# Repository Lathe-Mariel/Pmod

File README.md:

# Pmod
 Pmod boards
# KiCADのプロジェクト
各ボードは，KiCADのプロジェクトを含みます．  
ガーバーデータは 'output' ディレクトリに入っています．  
Each Pmod board directory has KiCAD project file and garber data.

写真 | ボード | 説明 | その他
---|---|---|---
 | Pmod_7Seg | 7セグLED6桁 | Pmodダブル
 | Pmod_encoder | ロータリエンコーダ | Digilent互換
 | Pmod_PLED | パワーLED | 片面アルミ基板
 | Sugamod_Matrix2 <a href="https://github.com/Lathe-Mariel/Pmod/tree/main/Pmod_Matrix2/output/output.zip">garber file</a> | 2色8x8マトリクスLED | Pmod規格外，6層基板
 | Pmod_A4988 | ステッピングモータドライバA4988
 | Pmod_7LED_8digit | 7セグLED8桁 | 4桁7セグモジュール×2個使用
 | Pmod_US_Speaker | 超音波浮揚 | 超音波トランスジューサ×6モジュール
 | Pmod_Matrix256 | 16x16マトリクスLED | 秋月横長マトリクスLED
 | Pmod_ADC | 10bit 8ch A-Dコンバータ | MCP3008/MCP3208
 | Pmod_SC1602 | 16桁2行キャラクタディスプレー | データ4ビット
 | Pmod_CAN | CAN | TJA1441AT

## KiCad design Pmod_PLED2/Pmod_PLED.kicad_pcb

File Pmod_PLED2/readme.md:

# Pmod Power_ColorLED
 KiCADのプロジェクトになっています．  

 アルミの片面基板を想定しており，JLCPCBで制作後，動作確認してあります．

# BOM

## SS2040FL ショットキダイオード
RGBのうち，RだけVfが低いのでバランス取りとして入れています．  
RGB間の出力もPWMで調整する場合は，ソルダージャンパ直結でヨシッ！

# はんだ付け
アルミ基板なので，まぁ付かないです．  
筆者はホットプレート（100℃設定）に基板を置いた状態ではんだこてで手付けしています．  
はんだこてだけでは，かなり厳しいでしょう．  

# サンプルプログラム
サンプルプログラムです．  
Gowin EDAのプロジェクトになっています．

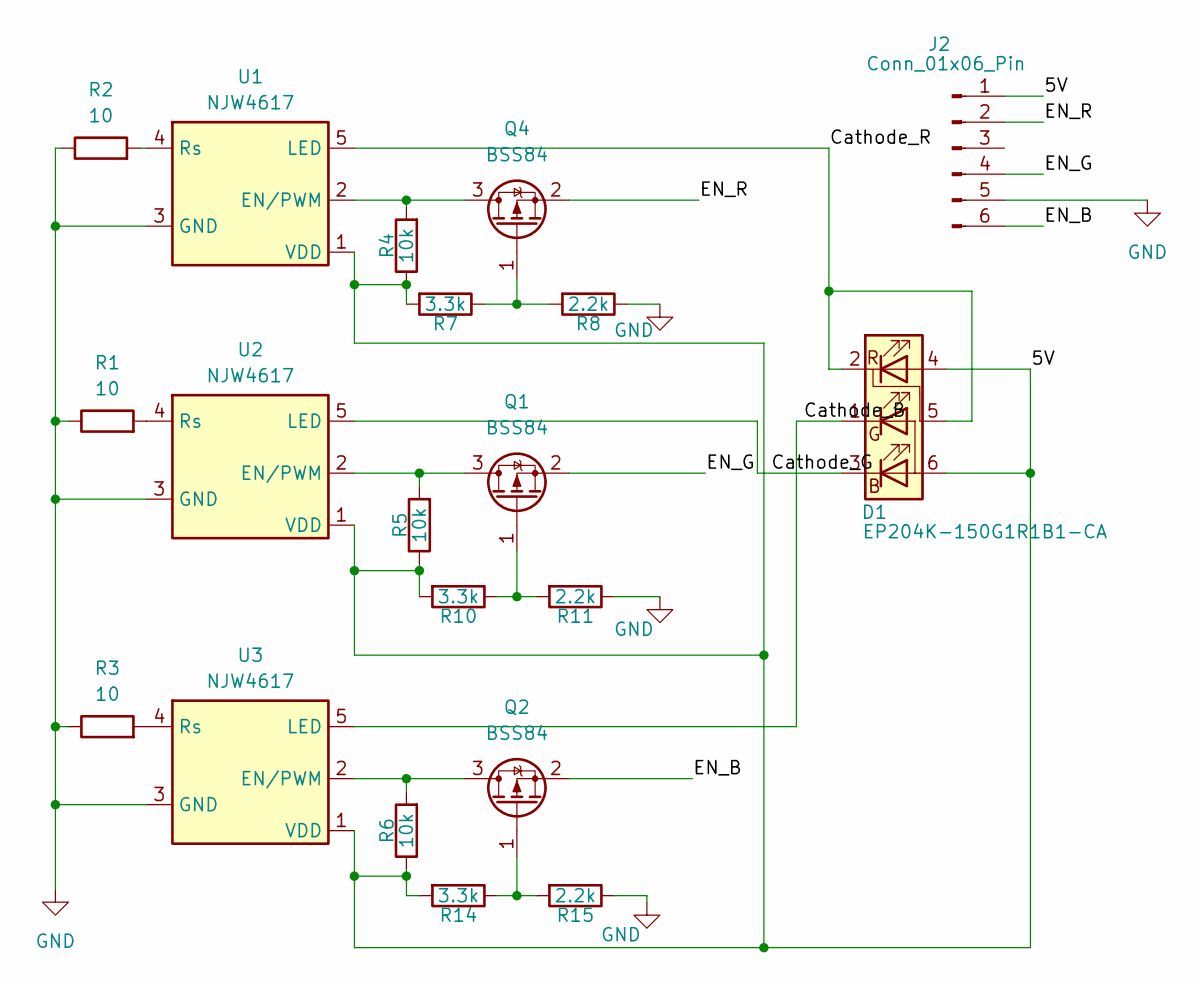
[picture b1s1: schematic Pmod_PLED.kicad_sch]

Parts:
D1: EP204K-150G1R1B1-CA; EP204-150G1R1B1-CA
J2: Conn_01x06_Pin; PinHeader_1x06_P2.54mm_Vertical_SMD_Pin1Left
Q1, Q2, Q4: BSS84; TSOT-23_HandSoldering
R1, R2, R3: 10; R_0603_1608Metric_Pad0.98x0.95mm_HandSolder
R4, R5, R6: 10k; R_0603_1608Metric_Pad0.98x0.95mm_HandSolder
R7, R10, R14: 3.3k; R_0603_1608Metric_Pad0.98x0.95mm_HandSolder
R8, R11, R15: 2.2k; R_0603_1608Metric_Pad0.98x0.95mm_HandSolder
U1, U2, U3: NJW4617; TO-252-5_TabPin3

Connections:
/5V: D1.4 (RA), D1.6 (A), J2.1, R4.1, R5.1, R6.1, R7.2, R10.2, R14.2, U1.1 (VDD), U2.1 (VDD), U3.1 (VDD)
/Cathode_B: D1.1 (GK), U3.5 (LED)
/Cathode_G: D1.3 (BK), U2.5 (LED)
/Cathode_R: D1.2 (RK), D1.5 (RK), U1.5 (LED)
/EN_B: J2.6, Q2.2 (S)
/EN_G: J2.4, Q1.2 (S)
/EN_R: J2.2, Q4.2 (S)
GND: J2.5, R1.1, R2.1, R3.1, R8.1, R11.1, R15.1, U1.3 (GND), U2.3 (GND), U3.3 (GND)
unnamed: Q1.3 (D), R5.2, U2.2 (EN/PWM)
unnamed: Q1.1 (G), R10.1, R11.2
unnamed: Q2.3 (D), R6.2, U3.2 (EN/PWM)
unnamed: Q2.1 (G), R14.1, R15.2
unnamed: Q4.3 (D), R4.2, U1.2 (EN/PWM)
unnamed: Q4.1 (G), R7.1, R8.2
unnamed: R2.2, U1.4 (Rs)
unnamed: R1.2, U2.4 (Rs)
unnamed: R3.2, U3.4 (Rs)

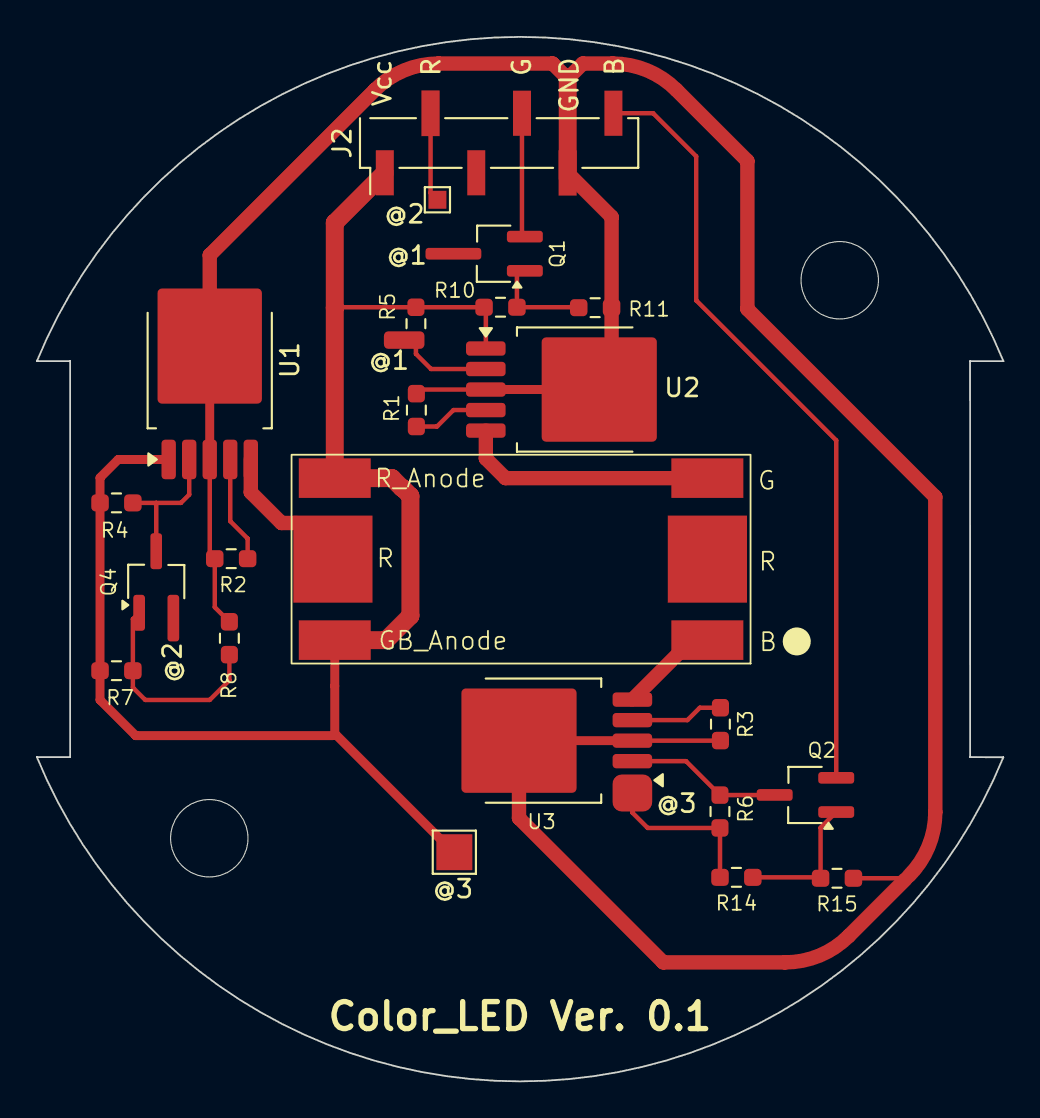
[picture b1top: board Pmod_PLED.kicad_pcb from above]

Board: 2 copper layers, 53.7 x 58.0 mm, 20 parts (0 on the bottom side), 17 nets.

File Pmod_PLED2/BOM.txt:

RoHS2(改正RoHS) (EU)2015/863、10物質、付属品等を除く
表面実装用ピンヘッダ　４０Ｐ　（２×２０）
[2213SM-40G]
1F 12 売場 キャビネット下段



在庫限り・見切り品・処分品
照明用大型フルカラーＬＥＤ　ハイパワー品　ＥＰ２０４Ｋ－１５０Ｇ１Ｒ１Ｂ１－ＣＡ
2021/11/29 500→200円、処分特価!
[EP204K-150G1R1B1-CA]
店員にお問い合わせください



PWM調光機能付き定電流LEDドライバー NJW4617DL3

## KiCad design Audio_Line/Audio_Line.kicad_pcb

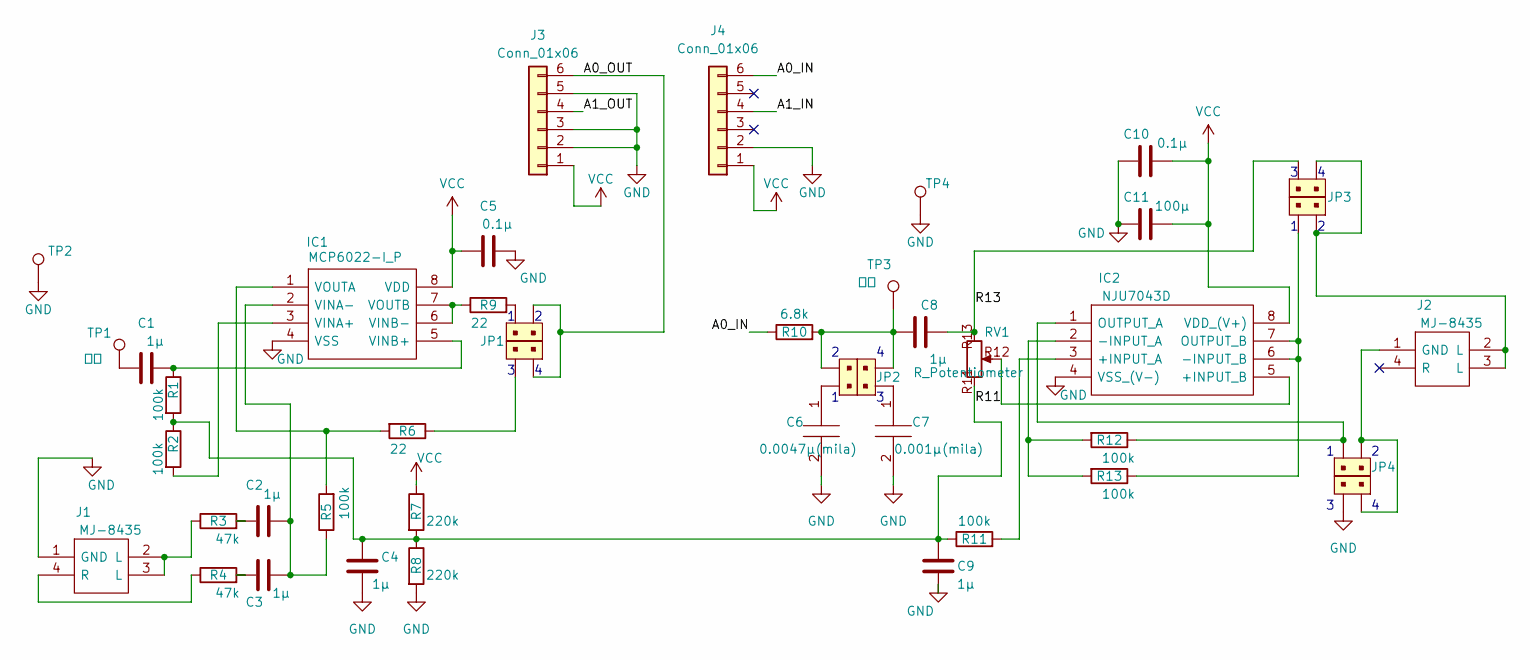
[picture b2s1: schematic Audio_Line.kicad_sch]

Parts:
C1, C2, C3, C4, C8, C9: 1μ; C_0603_1608Metric_Pad1.08x0.95mm_HandSolder
C5, C10: 0.1μ; C_0603_1608Metric_Pad1.08x0.95mm_HandSolder
C6: 0.0047μ(mila); C_Rect_L7.0mm_W2.0mm_P5.00mm; Manufacturer_Part_Number ECQUBAF332MA
C7: 0.001μ(mila); C_Rect_L7.0mm_W3.5mm_P5.00mm; Manufacturer_Part_Number ECQUBAF332MA
C11: 100μ; CP_Radial_D5.0mm_P2.50mm
IC1: MCP6022-I_P; DIP794W56P254L946H432Q8N; Manufacturer_Part_Number MCP6022-I/P
IC2: NJU7043D; DIP762W56P254L880H425Q8N; Manufacturer_Part_Number NJU7043D; Mouser Part Number 513-NJU7043D
J1, J2: MJ-8435; Manufacturer_Part_Number MJ-8435
J3, J4: Conn_01x06; PinHeader_1x06_P2.54mm_Horizontal
JP1, JP2, JP3, JP4, JP11, JP12, JP13, JP14: 22-23-2021; PinHeader_1x02_P2.54mm_Vertical; MPN 22-23-2021; Digi-Key_PN WM4200-ND
R1, R2, R5, R11, R12, R13: 100k; C_0603_1608Metric_Pad1.08x0.95mm_HandSolder
R3, R4: 47k; C_0603_1608Metric_Pad1.08x0.95mm_HandSolder
R6, R9: 22; C_0603_1608Metric_Pad1.08x0.95mm_HandSolder
R7, R8: 220k; C_0603_1608Metric_Pad1.08x0.95mm_HandSolder
R10: 6.8k; C_0603_1608Metric_Pad1.08x0.95mm_HandSolder
RV1: R_Potentiometer; RK09712200HA
TP1: 入力; TestPoint_Loop_D2.50mm_Drill1.0mm
TP2, TP4: TestPoint; TestPoint_Loop_D2.50mm_Drill1.0mm
TP3: 出力; TestPoint_Loop_D2.50mm_Drill1.0mm

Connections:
/A0_IN: J4.6, R10.1
/A0_OUT: J3.6, JP1.2, JP11.1
/A1_IN: J4.4
/A1_OUT: J3.4
/R11: C4.2, C9.2, R1.2, R2.1, R7.2, R8.1, R11.1, RV1.R11 (1)
/R13: C8.2, JP3.1, RV1.R13 (3)
GND: C4.1, C5.1, C6.2, C7.2, C9.1, C10.1, C11.1, IC1.4 (VSS), IC2.4 (VSS_(V-)), J1.1 (GND), J3.2, J3.3, J3.5, J4.2, JP14.2, R8.2, TP2.1, TP4.1
unnamed: C1.2, TP1.1
unnamed: C2.1, R3.2
unnamed: C3.1, R4.2
unnamed: C6.1, JP2.1
unnamed: C7.1, JP12.1
unnamed: C8.1, JP2.2, JP12.2, R10.2, TP3.1
unnamed: IC1.3 (VINA+), R2.2
unnamed: C2.2, C3.2, IC1.2 (VINA-), R5.1
unnamed: C1.1, IC1.5 (VINB+), R1.1
unnamed: IC1.6 (VINB-), IC1.7 (VOUTB), R9.1
unnamed: IC1.1 (VOUTA), R5.2, R6.2
unnamed: IC2.3 (+INPUT_A), R11.2
unnamed: IC2.5 (+INPUT_B), RV1.R12 (2)
unnamed: IC2.2 (-INPUT_A), R12.2, R13.2
unnamed: IC2.6 (-INPUT_B), IC2.7 (OUTPUT_B), JP13.2, R13.1
unnamed: IC2.1 (OUTPUT_A), JP4.1, R12.1
unnamed: J1.2 (L), J1.3 (L), R3.1
unnamed: J1.4 (R), R4.1
unnamed: J2.1 (GND), JP4.2, JP14.1
unnamed: J2.2 (L), J2.3 (L), JP3.2, JP13.1
unnamed: JP1.1, R9.2
unnamed: JP11.2, R6.1
VCC: C5.2, C10.2, C11.2, IC1.8 (VDD), IC2.8 (VDD_(V+)), J3.1, J4.1, R7.1

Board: 2 copper layers, 43 parts (0 on the bottom side), 28 nets, no tracks yet.

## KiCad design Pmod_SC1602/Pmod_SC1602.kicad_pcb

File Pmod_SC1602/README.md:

output/ --------   Gerver data  
sample/ --------   sample project for FPGA  
Pmod_SC1602.kicat_pro ----   KiCAD project

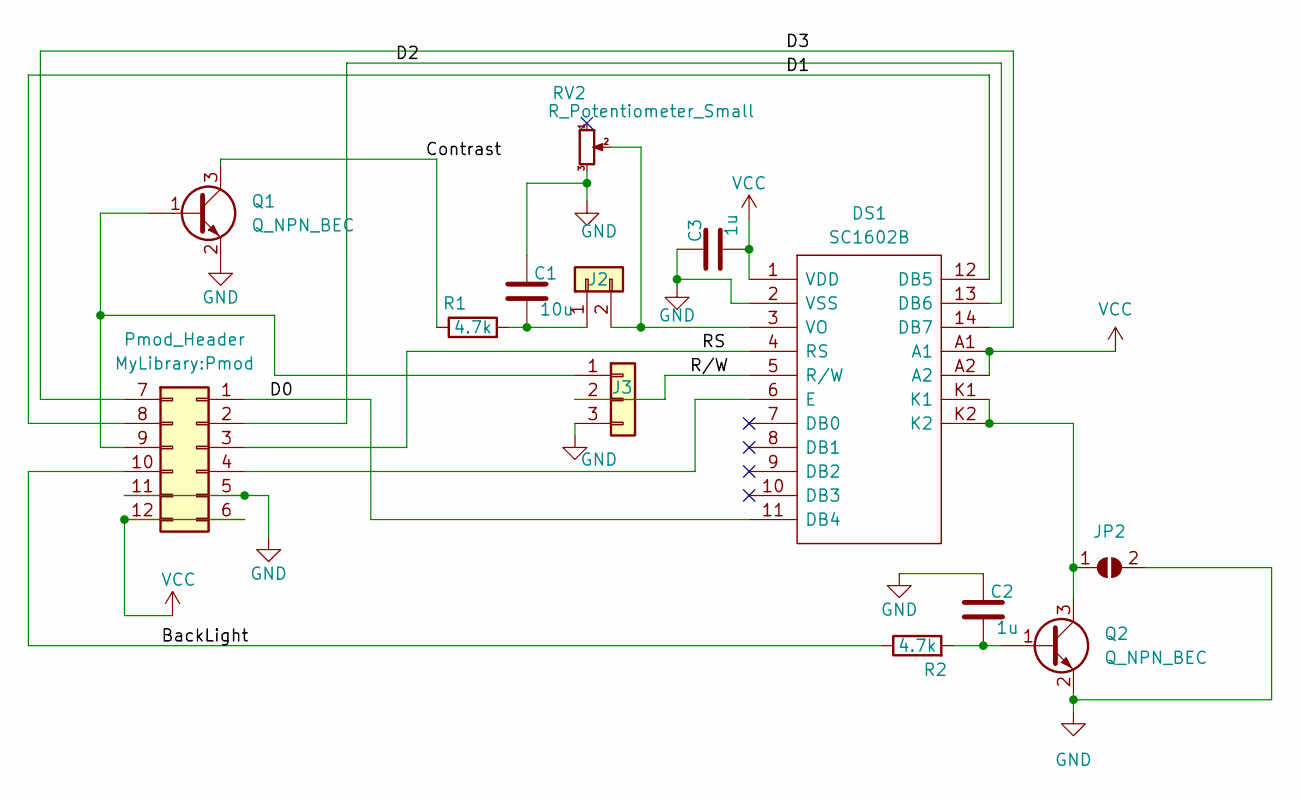
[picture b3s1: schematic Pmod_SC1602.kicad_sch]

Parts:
C1: 10u; C_0805_2012Metric_Pad1.18x1.45mm_HandSolder
C2, C3: 1u; C_0603_1608Metric_Pad1.08x0.95mm_HandSolder
DS1: SC1602B; Manufacturer_Part_Number SC1602B
J1: Pmod_Header; Pmod
J2: Conn_01x02; PinSocket_1x02_P2.54mm_Vertical
J3: Conn_01x03; PinSocket_1x03_P2.54mm_Vertical
JP2: SolderJumper_2_Open; SolderJumper-2_P1.3mm_Open_TrianglePad1.0x1.5mm
Q1, Q2: Q_NPN_BEC; SC-59_Handsoldering
R1, R2: 4.7k; R_0603_1608Metric_Pad0.98x0.95mm_HandSolder
RV2: R_Potentiometer_Small; Potentiometer_Vishay_T73XW_Horizontal

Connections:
/BackLight: J1.10, R2.1
/Contrast: Q1.3 (C), R1.1
/D0: DS1.11 (DB4), J1.1
/D1: DS1.12 (DB5), J1.8
/D2: DS1.13 (DB6), J1.2
/D3: DS1.14 (DB7), J1.7
/RS: DS1.4 (RS), J1.3
/R/W: DS1.5 (R/W), J3.2
GND: C1.2, C2.2, C3.2, DS1.2 (VSS), J1.5, J1.11, J3.3, JP2.2 (B), Q1.2 (E), Q2.2 (E), RV2.3
unnamed: DS1.6 (E), J1.4
unnamed: DS1.3 (VO), J2.2, RV2.2
unnamed: J1.9, J3.1, Q1.1 (B)
unnamed: C1.1, J2.1, R1.2
unnamed: DS1.K1, DS1.K2, JP2.1 (A), Q2.3 (C)
unnamed: C2.1, Q2.1 (B), R2.2
VCC: C3.1, DS1.1 (VDD), DS1.A1, DS1.A2, J1.6, J1.12

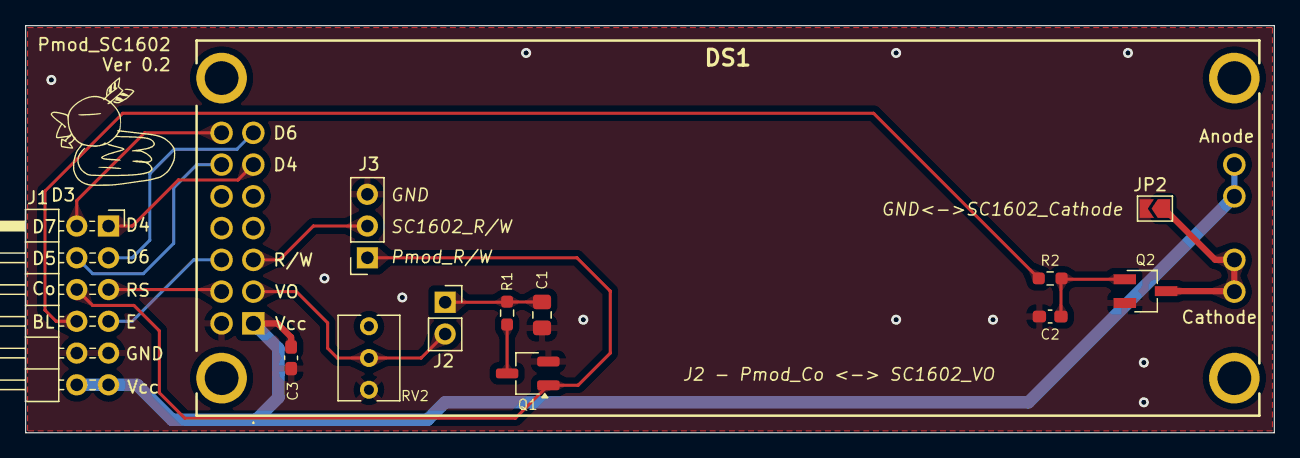
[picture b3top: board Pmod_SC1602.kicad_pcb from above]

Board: 2 copper layers, 99.9 x 32.6 mm, 13 parts (0 on the bottom side), 16 nets.

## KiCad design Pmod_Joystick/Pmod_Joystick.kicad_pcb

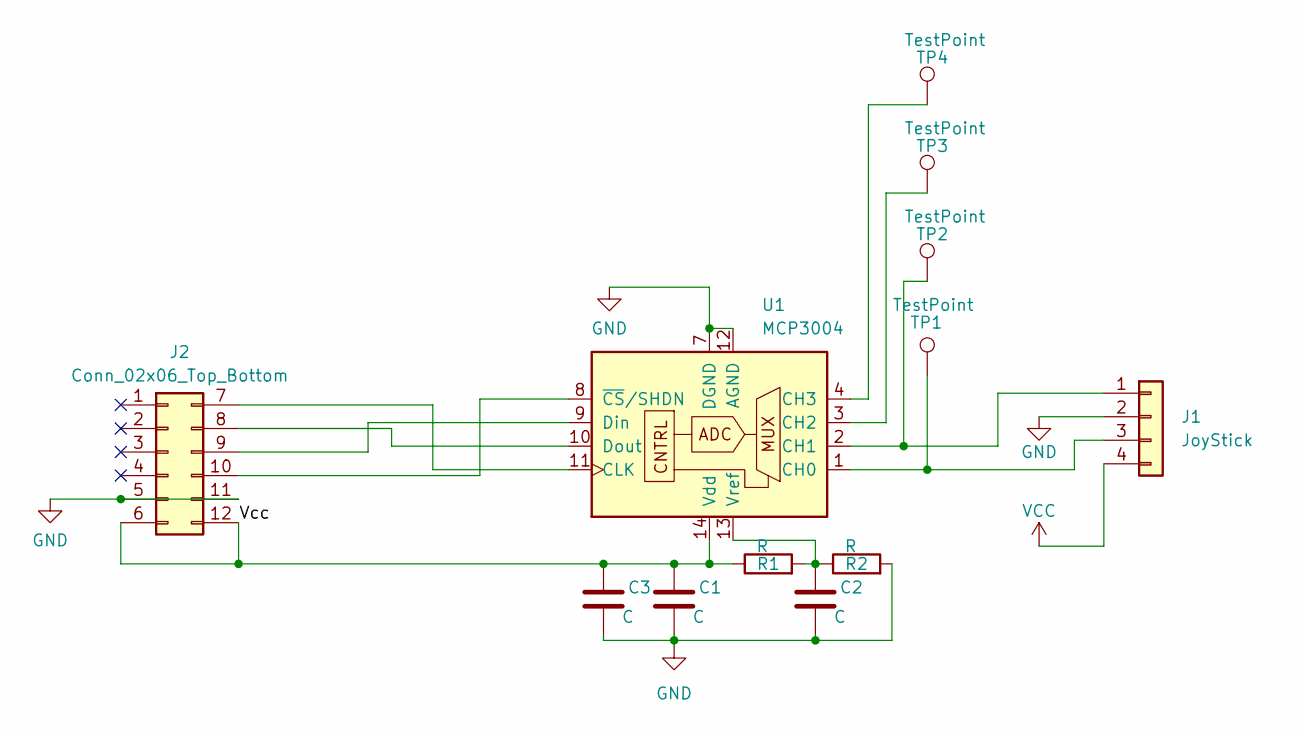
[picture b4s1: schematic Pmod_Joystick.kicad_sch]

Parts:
C1, C2, C3: C; C_0603_1608Metric_Pad1.08x0.95mm_HandSolder
J1: JoyStick; PSP1000_Joystick
J2: Conn_02x06_Top_Bottom; PinSocket_2x06_P2.54mm_Horizontal
R1, R2: R; R_0603_1608Metric_Pad0.98x0.95mm_HandSolder
TP1, TP2, TP3, TP4: TestPoint; TestPoint_THTPad_D1.5mm_Drill0.7mm
U1: MCP3004; TSSOP-14_4.4x5mm_P0.65mm

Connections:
GND: C1.2, C2.2, C3.2, J1.2 (Y), J2.5, J2.11, R2.2, U1.7 (DGND), U1.12 (AGND)
unnamed: J1.3 (GND), TP1.1, U1.1 (CH0)
unnamed: J1.1 (Vcc), TP2.1, U1.2 (CH1)
unnamed: J2.7, U1.11 (CLK)
unnamed: J2.8, U1.10 (Dout)
unnamed: J2.9, U1.9 (Din)
unnamed: J2.10, U1.8 (~CS/SHDN)
unnamed: C1.1, C3.1, J2.6, J2.12, R1.1, U1.14 (Vdd)
unnamed: TP3.1, U1.3 (CH2)
unnamed: TP4.1, U1.4 (CH3)
unnamed: C2.1, R1.2, R2.1, U1.13 (Vref)
VCC: J1.4 (Y)

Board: 2 copper layers, 12 parts (0 on the bottom side), 11 nets, no tracks yet.

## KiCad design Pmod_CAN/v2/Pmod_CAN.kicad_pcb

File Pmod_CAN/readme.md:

# Pmod CAN V2

# Schematics

# BoM

部品(Item) | 内容 | 数量(Qauntity)
--|--|--
チップ抵抗 | 1608 4.7K | 4 | LED(1)，CAN(3)
チップ抵抗 | 1608 10K | 1 | LED
チップ抵抗 | 1608 1/3W 60.4 | 2 | CAN
チップコンデンサ| 1608 0.1μ | 1 | CAN
チップコンデンサ| 1608 10μ | 1 | CAN
チップコンデンサ| 1608 4.7n | 1 | CAN
LED | WS2812B (I-07915) | 3| LED
チップトランジスタ | 2SC3325-Y(I-00628) | 1| LED
AE-XC9306-5V0(秋月) | 昇降圧DC-DCコンバータ | 1 | LED/CAN
ピンヘッダ | アングル・ピンヘッダ(2x6) | 1 | LED/CAN
CANトランシーバ | TJA1441AT(NXP) | 1 | CAN
TVS | | CAN
コモンモードチョークコイル | SDCW3216-2-222TF | CAN
# Sample
　sampleディレクトリにサンプルのFPGA用プロジェクトが入っています．

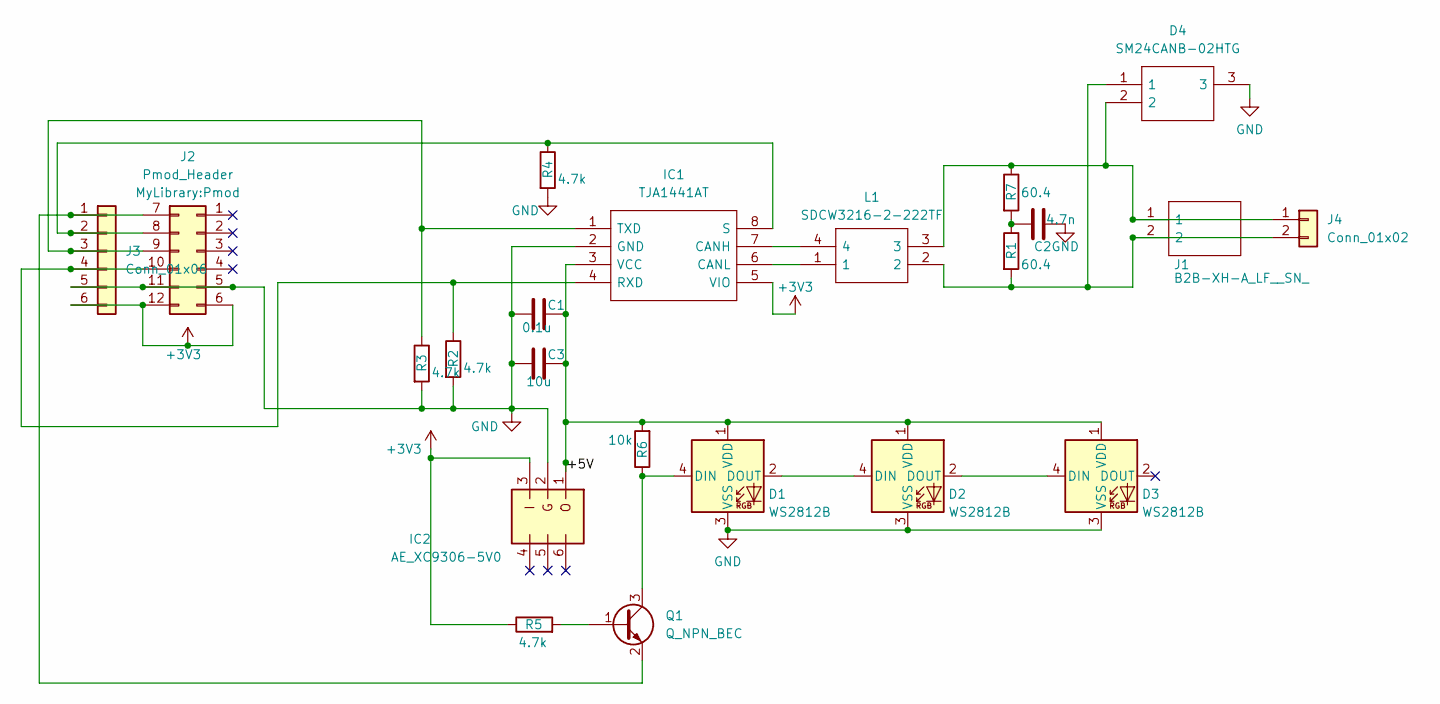
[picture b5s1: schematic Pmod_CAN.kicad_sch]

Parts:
C1: 0.1u; C_0603_1608Metric_Pad1.08x0.95mm_HandSolder
C2: 4.7n; C_0603_1608Metric_Pad1.08x0.95mm_HandSolder
C3: 10u; C_0603_1608Metric_Pad1.08x0.95mm_HandSolder
D1, D2, D3: WS2812B; LED_WS2812B_PLCC4_5.0x5.0mm_P3.2mm
D4: SM24CANB-02HTG; SM24CANB02HTG; Manufacturer_Part_Number SM24CANB-02HTG
IC1: TJA1441AT; SOIC127P600X175-8N; Manufacturer_Part_Number TJA1441AT
IC2: AE_XC9306-5V0; AE-XC9306-5V0
J1: B2B-XH-A_LF__SN_; SHDR2W64P0X250_1X2_740X575X700P; Manufacturer_Part_Number B2B-XH-A(LF)(SN)
J2: Pmod_Header; Pmod
J3: Conn_01x06; PinHeader_1x06_P2.54mm_Vertical
J4: Conn_01x02; PinHeader_1x02_P2.54mm_Vertical
L1: SDCW3216-2-222TF; SDCW32162222TF; Manufacturer_Part_Number SDCW3216-2-222TF
Q1: Q_NPN_BEC; SC-59_Handsoldering
R1, R7: 60.4; R_0603_1608Metric_Pad0.98x0.95mm_HandSolder
R2, R3, R4, R5: 4.7k; R_0603_1608Metric_Pad0.98x0.95mm_HandSolder
R6: 10k; R_0603_1608Metric_Pad0.98x0.95mm_HandSolder

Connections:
+3V3: IC1.5 (VIO), IC2.3, J2.6, J2.12, J3.6, R5.1
/+5V: C1.2, C3.2, D1.1 (VDD), D2.1 (VDD), D3.1 (VDD), IC1.3 (VCC), IC2.1, R6.2
GND: C1.1, C2.2, C3.1, D1.3 (VSS), D2.3 (VSS), D3.3 (VSS), D4.3, IC1.2 (GND), IC2.2 (G), IC2.5 (G), J2.5, J2.11, J3.5, R2.2, R3.2, R4.2
unnamed: C2.1, R1.1, R7.2
unnamed: D1.4 (DIN), Q1.3 (C), R6.1
unnamed: D1.2 (DOUT), D2.4 (DIN)
unnamed: D2.2 (DOUT), D3.4 (DIN)
unnamed: IC1.7 (CANH), L1.4
unnamed: IC1.6 (CANL), L1.1
unnamed: IC1.4 (RXD), J2.10, J3.4, R2.1
unnamed: IC1.8 (S), J2.8, J3.2, R4.1
unnamed: IC1.1 (TXD), J2.9, J3.3, R3.1
unnamed: J2.7, J3.1, Q1.2 (E)
unnamed: D4.2, J1.1, J4.1, L1.3, R7.1
unnamed: D4.1, J1.2, J4.2, L1.2, R1.2
unnamed: Q1.1 (B), R5.2

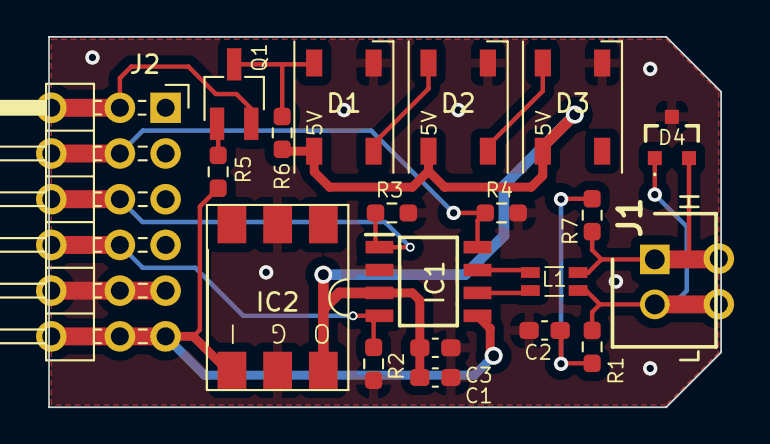
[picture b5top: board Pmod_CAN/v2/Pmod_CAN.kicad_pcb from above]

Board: 2 copper layers, 37.3 x 20.6 mm, 22 parts (0 on the bottom side), 16 nets.

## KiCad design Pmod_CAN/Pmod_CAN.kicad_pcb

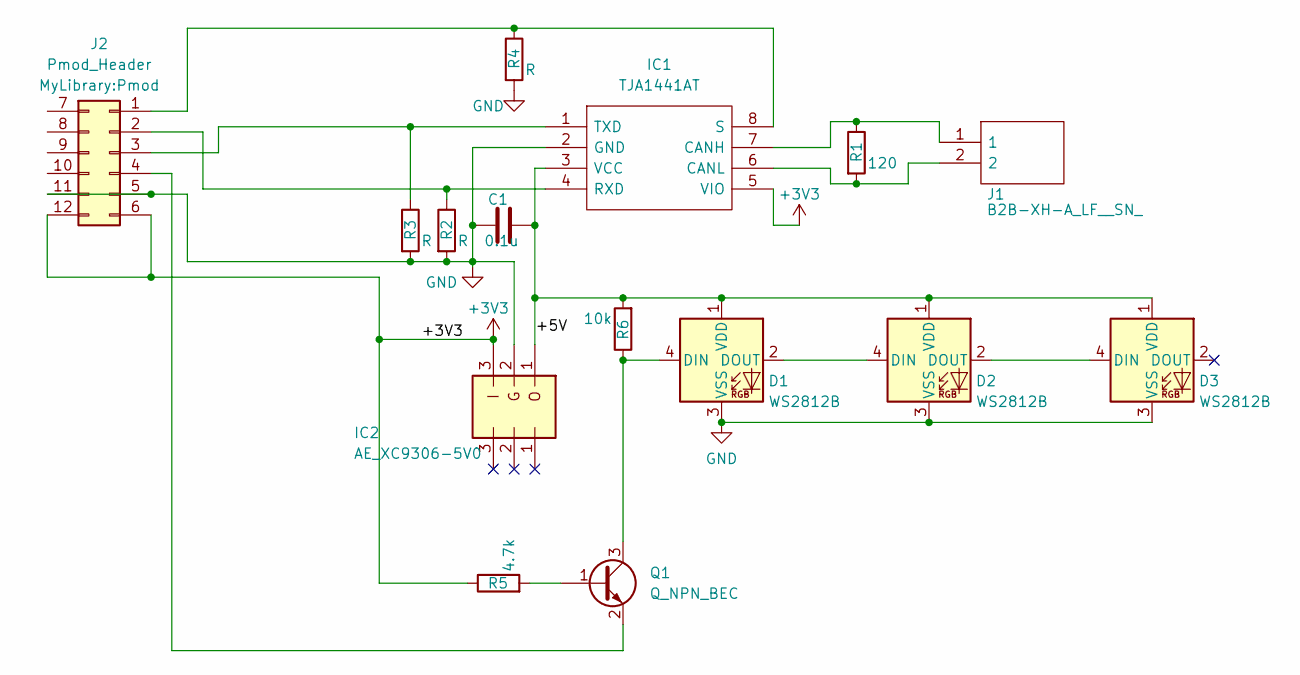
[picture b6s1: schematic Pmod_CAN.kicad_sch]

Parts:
C1: 0.1u; C_0603_1608Metric_Pad1.08x0.95mm_HandSolder
D1: WS2812B; R_Axial_DIN0309_L9.0mm_D3.2mm_P2.54mm_Vertical
D2, D3: WS2812B; LED_WS2812B_PLCC4_5.0x5.0mm_P3.2mm
IC1: TJA1441AT; SOIC127P600X175-8N; Manufacturer_Part_Number TJA1441AT
IC2: AE_XC9306-5V0; AE-XC9306-5V0
J1: B2B-XH-A_LF__SN_; SHDR2W64P0X250_1X2_740X575X700P; Manufacturer_Part_Number B2B-XH-A(LF)(SN)
J2: Pmod_Header; Pmod
Q1: Q_NPN_BEC; SC-59_Handsoldering
R1: 120; R_Axial_DIN0309_L9.0mm_D3.2mm_P2.54mm_Vertical
R2, R3, R4: R; R_0603_1608Metric_Pad0.98x0.95mm_HandSolder
R5: 4.7k; R_0603_1608Metric_Pad0.98x0.95mm_HandSolder
R6: 10k; R_0603_1608Metric_Pad0.98x0.95mm_HandSolder

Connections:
+3V3: IC1.5 (VIO), IC2.3 (I), J2.6, J2.12, R5.1
/+5V: C1.2, D1.1 (VDD), D2.1 (VDD), D3.1 (VDD), IC1.3 (VCC), IC2.1 (O), R6.2
GND: C1.1, D1.3 (VSS), D2.3 (VSS), D3.3 (VSS), IC1.2 (GND), IC2.2 (G), J2.5, J2.11, R2.2, R3.2, R4.2
unnamed: D1.4 (DIN), Q1.3 (C), R6.1
unnamed: D1.2 (DOUT), D2.4 (DIN)
unnamed: D2.2 (DOUT), D3.4 (DIN)
unnamed: IC1.7 (CANH), J1.1, R1.1
unnamed: IC1.6 (CANL), J1.2, R1.2
unnamed: IC1.4 (RXD), J2.2, R2.1
unnamed: IC1.8 (S), J2.1, R4.1
unnamed: IC1.1 (TXD), J2.3, R3.1
unnamed: J2.4, Q1.2 (E)
unnamed: Q1.1 (B), R5.2

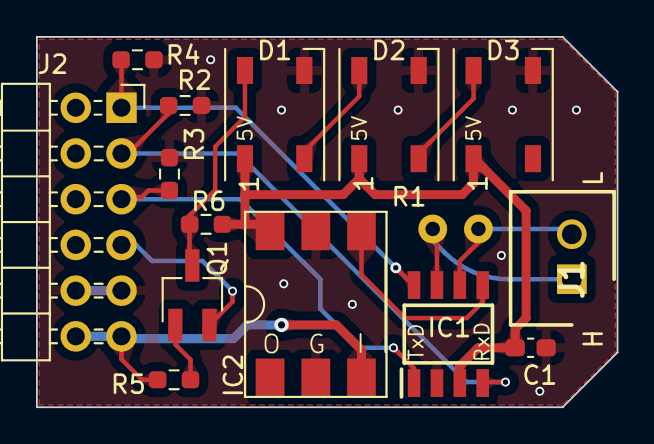
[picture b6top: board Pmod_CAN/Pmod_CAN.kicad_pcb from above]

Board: 2 copper layers, 32.3 x 20.6 mm, 15 parts (0 on the bottom side), 13 nets.

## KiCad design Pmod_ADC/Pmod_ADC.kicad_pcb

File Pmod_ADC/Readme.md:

KiCADで作ったPCBデータです．
Pmodに対応したA-Dコンバータ基板です．  

# Pmod_ADC
8チャネルのADコンバータ・チップ MCP3008/3208をPmodで使うボード．  
8チャネルのアナログ信号を入力できます．  
チャネル1（ch1）については，テストピンもしくはPhone Jackからも入力できます．  

# BoM
網羅はできていませんが，だいたいこんなものがあればよいのではないでしょうか．  

1806抵抗：22Ω，22kΩ，47kΩ  

回路 | 部品(Item) | 説明 | 数量(Qauntity) | No
---|---|---|---|---
U3  | MCP6492T-E/SN | オペアンプ | 1 | I-16239
TP1, TP2(GND) | TEST-1 | テスト端子 | 2 | 
R11, R12 | 金属皮膜チップ抵抗器 220kΩ | 金属皮膜チップ抵抗器1608 1/10W ±0.1% | 2 | 
R6, R7, R10 | チップ抵抗 100kΩ | チップ抵抗 1/10W 100k | 3 | 
R4, R5 | チップ抵抗 47kΩ | チップ抵抗 1/10W 47k | 2 | 
R8, R9 | チップ抵抗 22Ω | チップ抵抗 1/10W 22 | 2 | 
R1, R2 | チップ抵抗 10kΩ | チップ抵抗 1/10W 10k | 2（オプション） | 
J1 | ピンヘッダ | アングル・ピンヘッダ　ダブル(2x6) | 1 | 
C3, C4, C5, C7 | チップコンデンサ 1uF | 積層セラミックコンデンサ 1uF50V 1608 | 4 | 
C2, C6 | チップコンデンサ 0.1uF | 積層セラミックコンデンサ 0.1uF25V 1608 | 2 | 
RV1 | 半固定ボリューム | たて型 3296W 10k | 1（オプション）| P-08939
C1 | 電解コンデンサ | 電解コンデンサMH5 100uF16V | 1 | 
U3 | 10bit 8ch A-Dコンバータ | MCP3008-I/P  | 1 | 

# Schematics

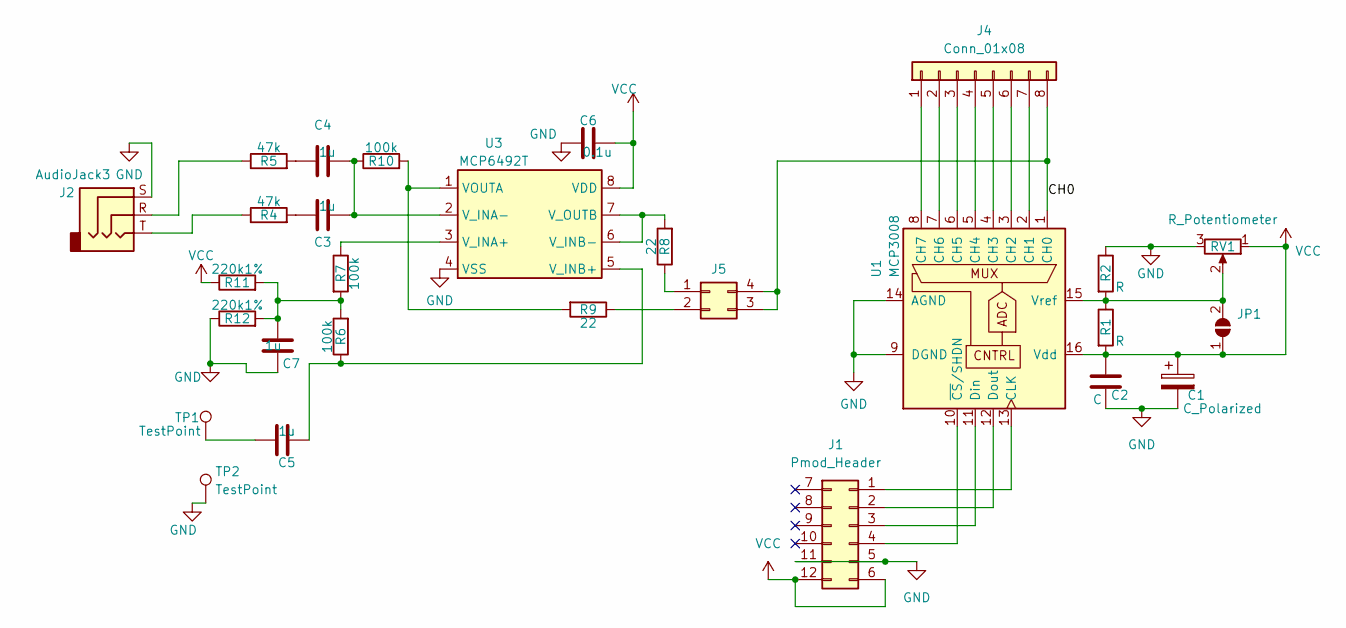
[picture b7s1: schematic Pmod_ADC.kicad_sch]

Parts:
C1: C_Polarized; CP_Radial_D8.0mm_P3.50mm
C2: C; C_0603_1608Metric_Pad1.08x0.95mm_HandSolder
C3, C4, C5, C7: 1u; C_0603_1608Metric_Pad1.08x0.95mm_HandSolder
C6: 0.1u; C_0603_1608Metric_Pad1.08x0.95mm_HandSolder
J1: Pmod_Header; PinHeader_2x06_P2.54mm_Horizontal
J2: AudioJack3; Jack_3.5mm_Switronic_ST-005-G_horizontal
J4: Conn_01x08; TerminalBlock_RND_205-00238_1x08_P5.08mm_Horizontal
J5: Conn_02x02_Counter_Clockwise; PinHeader_2x02_P2.54mm_Vertical
JP1: SolderJumper_2_Open; SolderJumper-2_P1.3mm_Open_TrianglePad1.0x1.5mm
R1, R2: R; R_0603_1608Metric_Pad0.98x0.95mm_HandSolder
R4, R5: 47k; R_0603_1608Metric_Pad0.98x0.95mm_HandSolder
R6, R7, R10: 100k; R_0603_1608Metric_Pad0.98x0.95mm_HandSolder
R8, R9: 22; R_0603_1608Metric_Pad0.98x0.95mm_HandSolder
R11, R12: 220k1%; R_0603_1608Metric_Pad0.98x0.95mm_HandSolder
RV1: R_Potentiometer; TSR3296W203R
TP1, TP2: TestPoint; TestPoint_THTPad_1.5x1.5mm_Drill0.7mm
U1: MCP3008; DIP-16_W7.62mm
U3: MCP6492T; SOIC-8_3.9x4.9mm_P1.27mm

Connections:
/CH0: J4.8, J5.3, J5.4, U1.1 (CH0)
GND: C1.2, C2.2, C6.2, C7.1, J1.5, J1.11, J2.S, R2.1, R12.1, RV1.3, TP2.1, U1.9 (DGND), U1.14 (AGND), U3.4 (VSS)
unnamed: C3.1, R4.2
unnamed: C4.1, R5.2
unnamed: C5.1, TP1.1
unnamed: C7.2, R6.2, R7.2, R11.2, R12.2
unnamed: J1.1, U1.13 (CLK)
unnamed: J1.2, U1.12 (Dout)
unnamed: J1.3, U1.11 (Din)
unnamed: J1.4, U1.10 (~CS/SHDN)
unnamed: J2.R, R5.1
unnamed: J2.T, R4.1
unnamed: J4.1, U1.8 (CH7)
unnamed: J4.2, U1.7 (CH6)
unnamed: J4.3, U1.6 (CH5)
unnamed: J4.4, U1.5 (CH4)
unnamed: J4.5, U1.4 (CH3)
unnamed: J4.6, U1.3 (CH2)
unnamed: J4.7, U1.2 (CH1)
unnamed: J5.1, R8.1
unnamed: J5.2, R9.1
unnamed: JP1.2 (B), R1.1, R2.2, RV1.2, U1.15 (Vref)
unnamed: R9.2, R10.2, U3.1 (VOUTA)
unnamed: R7.1, U3.3 (V_INA+)
unnamed: C3.2, C4.2, R10.1, U3.2 (V_INA-)
unnamed: C5.2, R6.1, U3.5 (V_INB+)
unnamed: R8.2, U3.6 (V_INB-), U3.7 (V_OUTB)
VCC: C1.1, C2.1, C6.1, J1.6, J1.12, JP1.1 (A), R1.2, R11.1, RV1.1, U1.16 (Vdd), U3.8 (VDD)

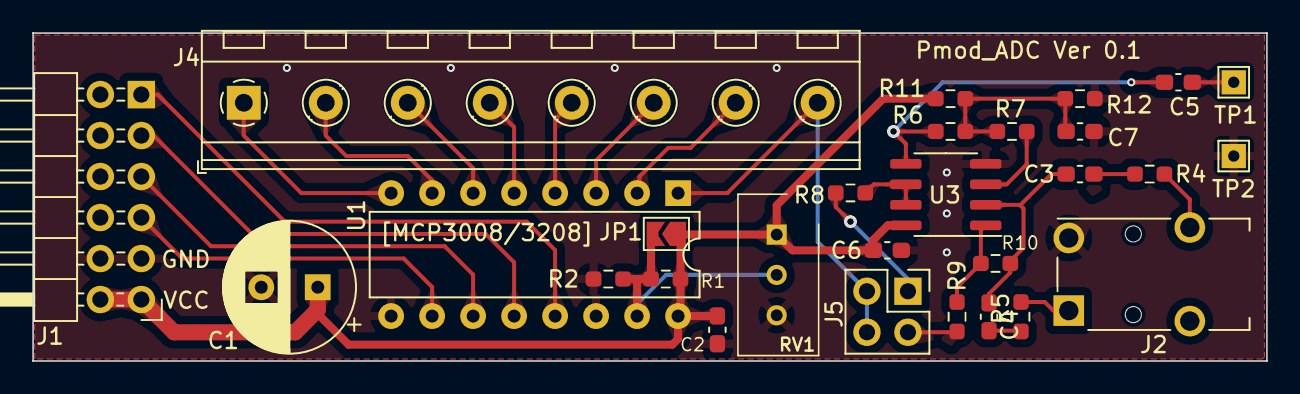
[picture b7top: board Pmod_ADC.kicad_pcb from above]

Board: 2 copper layers, 76.5 x 20.3 mm, 28 parts (0 on the bottom side), 28 nets.

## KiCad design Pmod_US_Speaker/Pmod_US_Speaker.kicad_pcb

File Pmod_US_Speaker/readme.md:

# Playing with Ultra Sonic
超音波浮揚で遊ぶPmodボードです．
2セット使うのがよいです．Upper BoardとLower Boardは同じ生基板を使います（超音波Speakerの取り付け方向が異なる）．

# BoM

部品 | 説明 | 数量
---|---|---
double pin header | Pmod header | 1
IR4428 | Gate Driver IC | 3
DC Jack(SMD) | DC Jack for driving speaker | 1
1608mm SMD Capaciter | chip capaciter 0.1μF V25 | 3
2012mm SMD Capaciter | chip capaciter 10μF V25 | 1

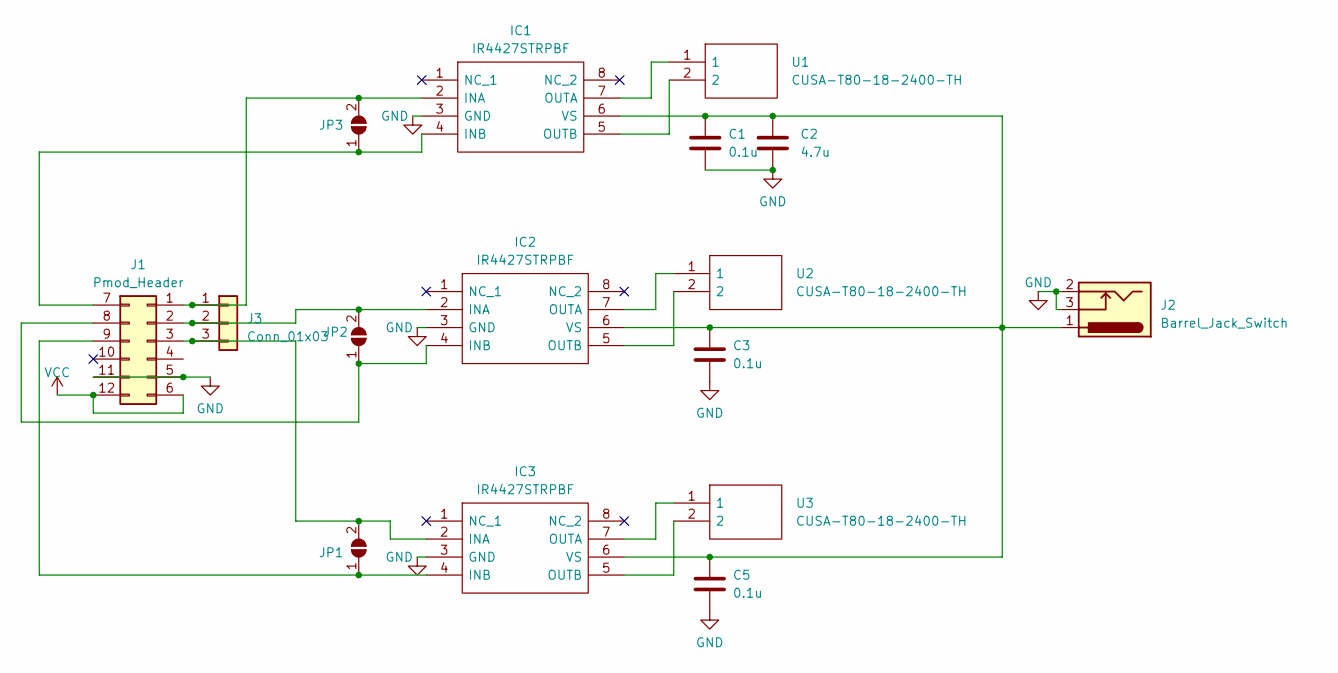
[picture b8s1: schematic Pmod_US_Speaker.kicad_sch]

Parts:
C1, C3, C5: 0.1u; C_0603_1608Metric_Pad1.08x0.95mm_HandSolder
C2: 4.7u; C_0805_2012Metric_Pad1.18x1.45mm_HandSolder
IC1, IC2, IC3: IR4427STRPBF; SOIC127P600X175-8N; Manufacturer_Part_Number IR4427STRPBF
J1: Pmod_Header; PinHeader_2x06_P2.54mm_Vertical
J2: Barrel_Jack_Switch; BarrelJack_CUI_PJ-036AH-SMT_Horizontal
J3: Conn_01x03; PinHeader_1x03_P2.54mm_Vertical
JP1, JP2, JP3: SolderJumper_2_Open; SolderJumper-2_P1.3mm_Open_TrianglePad1.0x1.5mm
U1, U2, U3: CUSA-T80-18-2400-TH; CUSAT80182400TH; Manufacturer_Part_Number CUSA-T80-18-2400-TH

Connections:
GND: C1.2, C2.2, C3.2, C5.2, IC1.3 (GND), IC2.3 (GND), IC3.3 (GND), J1.5, J1.11, J2.2, J2.3
unnamed: IC1.2 (INA), J1.1, J3.1, JP3.2 (B)
unnamed: IC1.4 (INB), J1.7, JP3.1 (A)
unnamed: IC1.7 (OUTA), U1.1
unnamed: IC1.5 (OUTB), U1.2
unnamed: C1.1, C2.1, C3.1, C5.1, IC1.6 (VS), IC2.6 (VS), IC3.6 (VS), J2.1
unnamed: IC2.2 (INA), J1.2, J3.2, JP2.2 (B)
unnamed: IC2.4 (INB), J1.8, JP2.1 (A)
unnamed: IC2.7 (OUTA), U2.1
unnamed: IC2.5 (OUTB), U2.2
unnamed: IC3.2 (INA), J1.3, J3.3, JP1.2 (B)
unnamed: IC3.4 (INB), J1.9, JP1.1 (A)
unnamed: IC3.7 (OUTA), U3.1
unnamed: IC3.5 (OUTB), U3.2
VCC: J1.6, J1.12

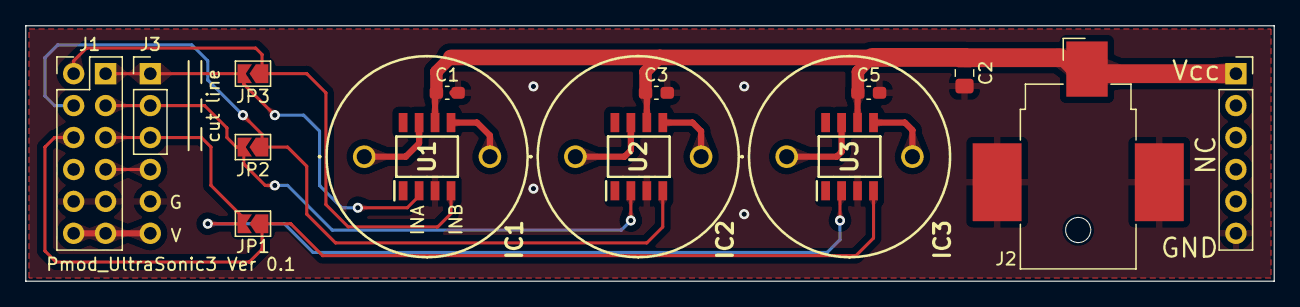
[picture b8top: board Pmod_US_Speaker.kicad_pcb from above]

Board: 2 copper layers, 99.3 x 20.3 mm, 16 parts (0 on the bottom side), 15 nets.

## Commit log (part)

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2023-06-01 601b
2023-06-01 601c
2023-06-01 601d
2023-06-30 630-2
2023-06-30 630-3
2023-07-04 704-2
2023-07-04 704-3
2023-07-04 704-4
2023-07-04 704-5
2023-07-04 704-6
2023-08-06 0807
2023-08-08 0809
2023-08-10 0810
2023-08-10 0811
2023-08-11 0812
2023-08-13 0813
2023-08-13 0814
2023-08-16 0816
2023-08-18 0818
2023-08-20 0820
2023-08-21 0821
2023-08-21 0822
2023-08-22 0822_2
2023-08-22 0822_3
2023-08-22 0822_4
2023-08-22 0823
2023-08-25 0825
2023-08-25 0826
2023-08-30 0830
2023-10-01 pmod adc
2023-10-10 1010
2023-10-20 1020
2023-10-27 1027
2023-10-27 1028
2023-10-30 1030
2023-10-30 1031
2023-11-06 1106
2023-11-06 1107
2023-11-13 1113
2023-11-14 1114
2023-11-20 1120
2023-11-21 add LED256 sample for Tang Primer 20K
2023-11-21 1122
2023-11-22 1123
2023-11-23 1124
2023-11-25 1125
2023-11-26 1127
2023-11-29 1129
2023-12-01 1201
2023-12-02 1202
2023-12-03 1204
2023-12-06 1206
2023-12-06 1207
2023-12-07 1208
2023-12-10 1210
2023-12-11 1211
2023-12-16 1217
2023-12-18 1218
2023-12-20 1220
2023-12-20 1221
2023-12-21 1222
2023-12-22 1223
2023-12-24 1225
2023-12-25 1226
2023-12-26 1227
2023-12-28 1228
2023-12-29 1229
2023-12-30 1230
2024-01-03 0104
2024-01-05 0105
2024-01-05 0106
2024-01-06 0107
2024-01-11 0111
2024-01-11 0112
2024-01-16 0117
2024-02-08 0208
2024-02-11 0211
2024-02-12 0213
2024-02-17 0218
2024-03-04 0304
2024-03-04 0305
2024-03-05 0306
2024-03-08 0309
2024-03-17 0318
2024-03-19 0319
2024-03-19 0320
2024-04-01 0401
2024-04-04 0404
2024-04-15 0416
2024-04-23 0423
2024-05-08 0509
2024-09-12 0912
2024-11-26 1126
2024-11-27 1128
2024-12-02 1203
2024-12-04 1205
2024-12-06 sc1602 update
2024-12-16 1216
2025-07-23 dual shock preparation
2025-07-24 audio_line
    PCB Pmod option board (for Digilent AD1, DA2)
2025-07-24 0724
2025-07-31 0731
2025-07-31 dual shock update
2025-08-09 dual shock2
2025-08-11 dual shock
2025-09-10 0910
2025-10-31 made pled2 project
2025-11-02 power led 2 schematics
2025-11-03 schematcis
2025-11-03 schematics
2025-11-09 1109
2025-11-09 1110
2025-11-21 1121
2026-01-17 8digit_7seg forgefpga
2026-01-18 forgefpga
2026-01-23 0124
2026-01-26 forge fpga 7seg 8digit done
2026-01-29 shrike lite matrix2
2026-01-30 shrike lite ledmatrix2
2026-01-31 shrike lite ledmatrix 2
2026-02-05 shrike lite matrixled2
2026-02-09 shrike lite2 matrix2
2026-02-11 matrix led2 sample shrike lite
2026-02-18 0219
2026-03-01 POMD_DTx2(sipeed)
2026-03-01 sc1602 forgeFPGA
2026-03-07 0307
2026-03-10 matrix2 readme update
2026-03-10 Fix typo in readme.md heading
2026-03-10 shrike lite file del
2026-03-20 sc1602 shrike lite
2026-03-22 sc1602 forgeFPGA sample
2026-03-22 fix 1 charactor
2026-03-24 0325
2026-03-24 Pmod TFTLCD
2026-03-25 0326
2026-03-26 0327
2026-03-27 ILI 9341 done
2026-03-28 bounce image
2026-03-30 pmod pin arrange
2026-03-30 color bar
2026-03-31 add specification data
2026-04-02 LED matrix
2026-04-02 shrike lite matrix led claude
2026-04-03 garbage collect
2026-04-06 Pmod_BLDC
2026-05-21 rotary encoder veryl
2026-05-21 0521
2026-05-21 veryl rotary encoder
2026-05-22 add debounce
2026-05-22 0523
2026-05-23 0524
2026-05-28 0529
2026-05-29 veryl rotary encoder sample done
2026-05-31 matrix led2 prompt
2026-06-02 sipeed pmod-led efinix t8 corsor
2026-06-04 pmod matrix256 sample
2026-06-06 for shrike lite
2026-06-08 pmod tft efinix
2026-06-08 tft efinix t8
2026-06-08 0609
2026-06-10 0611
2026-06-11 lcd efinix t8 done
2026-06-12 BLDC schematics
2026-06-13 tft touch
2026-06-13 lcd touch function
2026-06-14 lcd touch
2026-06-15 0615
2026-06-15 tftlcd efinix pin fix
2026-06-17 0617
2026-06-22 0622
